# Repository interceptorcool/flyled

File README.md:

# flyled
Fly Led controller for WS281x

# Manual for config - temp_config/conf_prototype.txt

main module esp8266

Libraries:

JsonFiles:
https://bblanchon.github.io/ArduinoJson

NeoPixelBus:
https://github.com/Makuna/NeoPixelBus

# change
global config: "INPUTS"

# add
action class: "RAND"

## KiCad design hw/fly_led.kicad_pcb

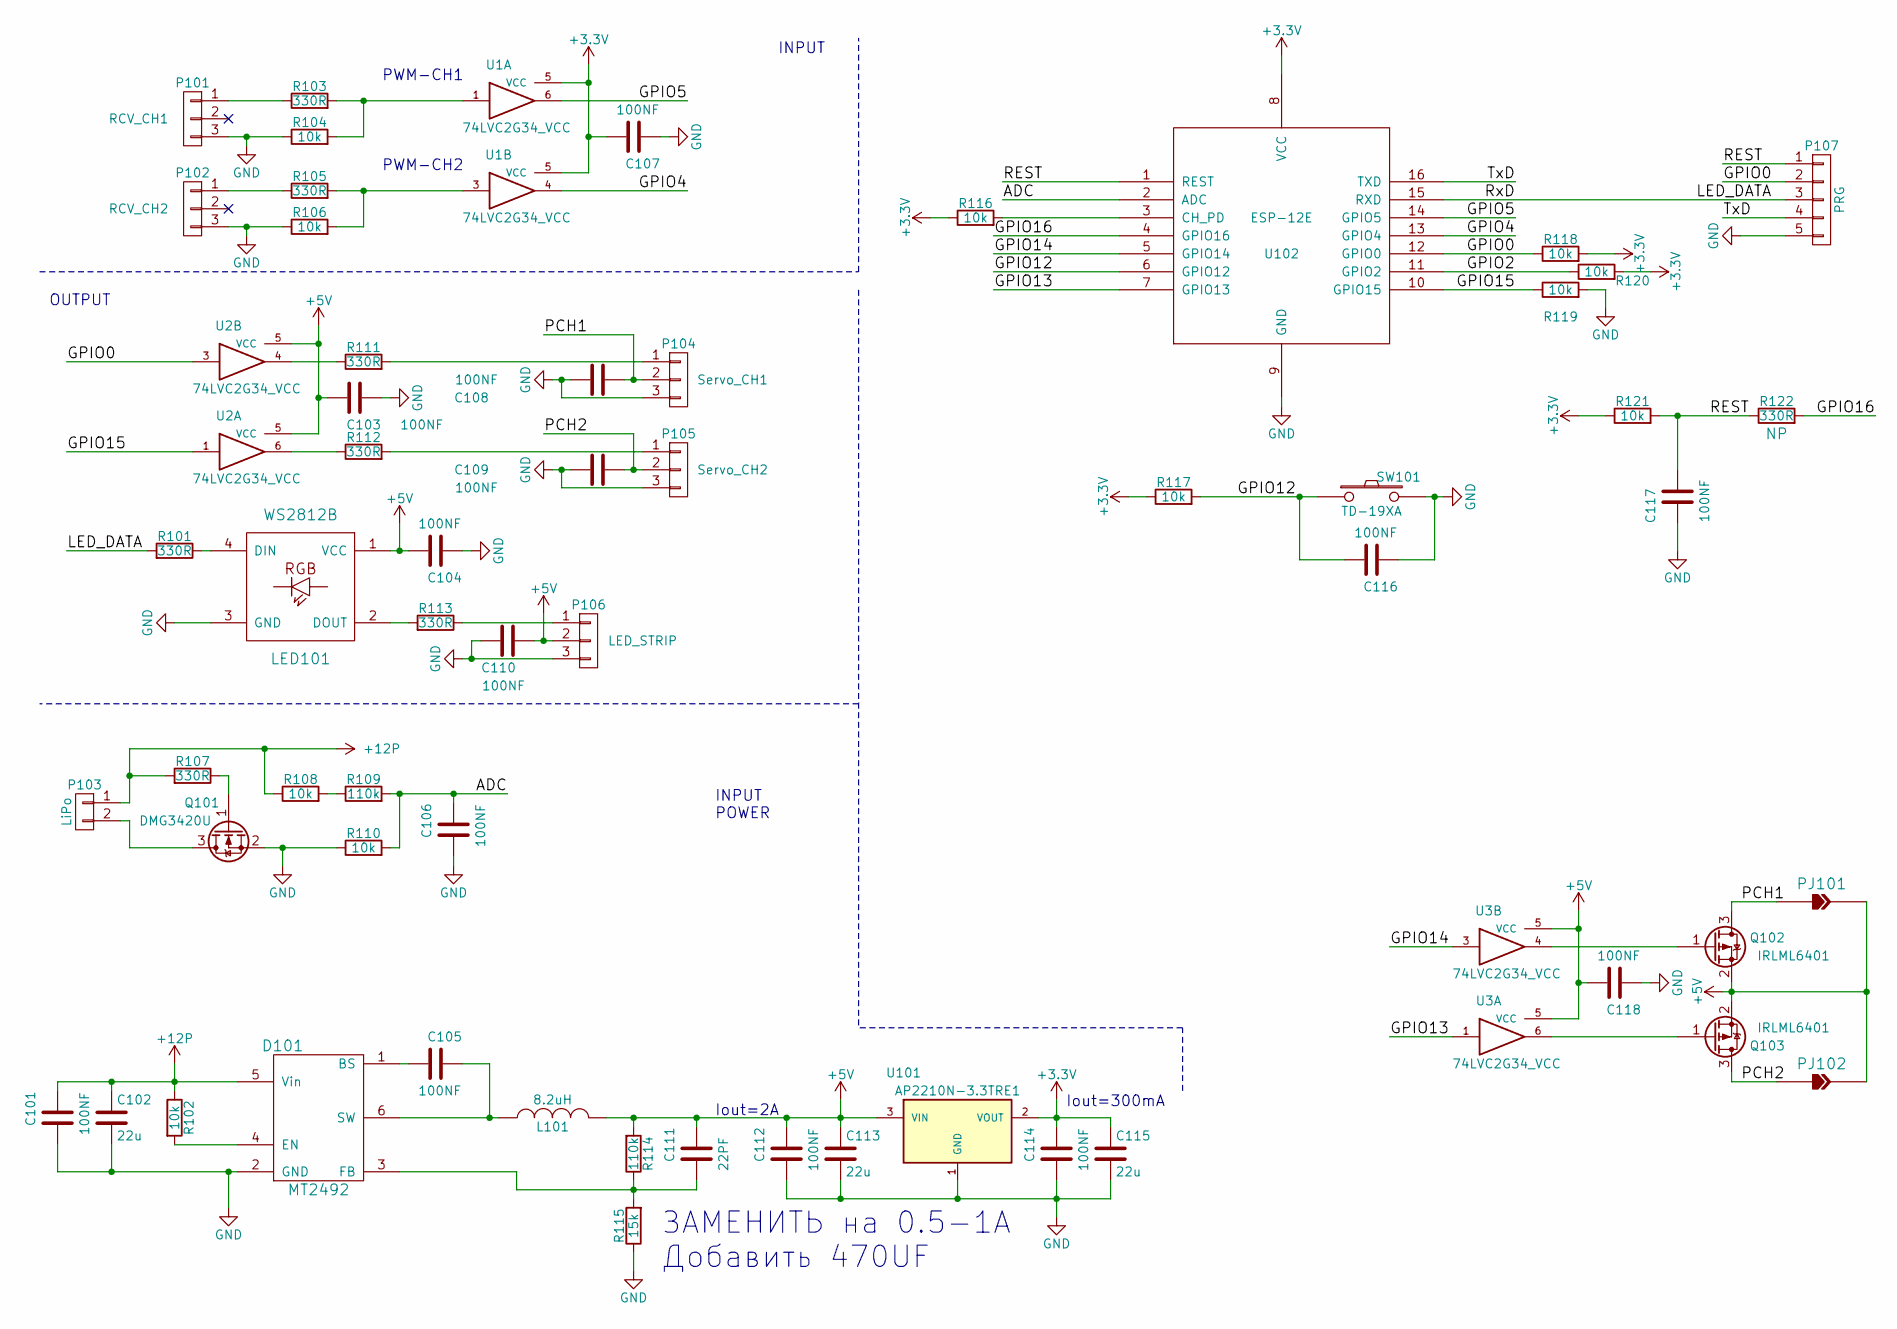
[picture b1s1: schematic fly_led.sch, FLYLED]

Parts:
C101, C103, C104, C105, C106, C107, C108, C109, C110, C112, C114, C116, C117, C118: 100NF; C_0603
C102, C113, C115: 22u; C_1210
C111: 22PF; C_0603
D101: MT2492; SOT-23-6
L101: 8.2uH; Choke_SMD_10.4x10.4_H4.8
LED101: WS2812B
P101: RCV_CH1; Pin_Header_Straight_1x03_Pitch2.54mm
P102: RCV_CH2; Pin_Header_Straight_1x03_Pitch2.54mm
P103: LiPo; Pin_Header_Straight_1x02_Pitch2.54mm
P104: Servo_CH1; Pin_Header_Straight_1x03_Pitch2.54mm
P105: Servo_CH2; Pin_Header_Straight_1x03_Pitch2.54mm
P106: LED_STRIP; Pin_Header_Straight_1x03_Pitch2.54mm
P107: PRG; Pin_Header_Straight_1x05_Pitch1.27mm
PJ101, PJ102: PJP; Jumper_SOL_HP
Q101: DMG3420U; SOT-23
Q102, Q103: IRLML6401; SOT-23
R101, R103, R105, R107, R111, R112, R113, R122: 330R; R_0603
R102, R104, R106, R108, R110, R116, R117, R118, R119, R120, R121: 10k; R_0603
R109, R114: 110k; R_0603
R115: 15k; R_0603
SW101: TD-19XA; SW_SPST_EVQPE1
U1, U2, U3: 74LVC2G34_VCC; SOT-363_SC-70-6
U101: AP2210N-3.3TRE1; SOT-23
U102: ESP-12E; ESP-12E-SMD

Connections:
+3V3: C107.2, C114.1, C115.1, R116.1, R117.1, R118.2, R120.2, R121.1, U1.5 (VCC), U101.2 (VOUT), U102.8 (VCC)
+5V: C103.2, C104.2, C110.2, C111.1, C112.1, C113.1, C118.2, L101.2, LED101.1 (VCC), P106.2, PJ101.2 (J2), PJ102.2 (J2), Q102.2 (S), Q103.2 (S), R114.2, U2.5 (VCC), U3.5 (VCC), U101.3 (VIN)
+12P: C101.1, C102.1, D101.5 (Vin), P103.1, R102.1, R107.2, R108.1
/ADC: C106.1, R109.2, R110.2, U102.2 (ADC)
/GPIO0: P107.2, R118.1, U2.3, U102.12 (GPIO0)
/GPIO2: R120.1, U102.11 (GPIO2)
/GPIO4: U1.4, U102.13 (GPIO4)
/GPIO5: U1.6, U102.14 (GPIO5)
/GPIO12: C116.2, R117.2, SW101.1, U102.6 (GPIO12)
/GPIO13: U3.1, U102.7 (GPIO13)
/GPIO14: U3.3, U102.5 (GPIO14)
/GPIO15: R119.1, U2.1, U102.10 (GPIO15)
/GPIO16: R122.2, U102.4 (GPIO16)
/LED_DATA: P107.3, R101.2, U102.15 (RXD)
/PCH1: C108.2, P104.2, PJ101.1 (J1), Q102.3 (D)
/PCH2: C109.2, P105.2, PJ102.1 (J1), Q103.3 (D)
/REST: C117.2, P107.1, R121.2, R122.1, U102.1 (REST)
/TxD: P107.4, U102.16 (TXD)
GND: C101.2, C102.2, C103.1, C104.1, C106.2, C107.1, C108.1, C109.1, C110.1, C112.2, C113.2, C114.2, C115.2, C116.1, C117.1, C118.1, D101.2 (GND), LED101.3 (GND), P101.3, P102.3, P104.3, P105.3, P106.3, P107.5, Q101.2 (S), R104.1, R106.1, R110.1, R115.1, R119.2, SW101.2, U1.2 (GND), U2.2 (GND), U3.2 (GND), U101.1 (GND), U102.9 (GND)
unnamed: C105.1, D101.6 (SW), L101.1
unnamed: C105.2, D101.1 (BS)
unnamed: C111.2, D101.3 (FB), R114.1, R115.2
unnamed: D101.4 (EN), R102.2
unnamed: LED101.2 (DOUT), R113.2
unnamed: LED101.4 (DIN), R101.1
unnamed: P101.1, R103.1
unnamed: P102.1, R105.1
unnamed: P103.2, Q101.3 (D)
unnamed: P104.1, R111.2
unnamed: P105.1, R112.2
unnamed: P106.1, R113.1
unnamed: Q101.1 (G), R107.1
unnamed: Q102.1 (G), U3.4
unnamed: Q103.1 (G), U3.6
unnamed: R103.2, R104.2, U1.1
unnamed: R105.2, R106.2, U1.3
unnamed: R108.2, R109.1
unnamed: R111.1, U2.4
unnamed: R112.1, U2.6
unnamed: R116.2, U102.3 (CH_PD)

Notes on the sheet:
PWM-CH1
PWM-CH2
INPUT
OUTPUT
INPUT POWER
Iout=2A
Iout=300mA
ЗАМЕНИТЬ на 0.5-1А Добавить 470UF

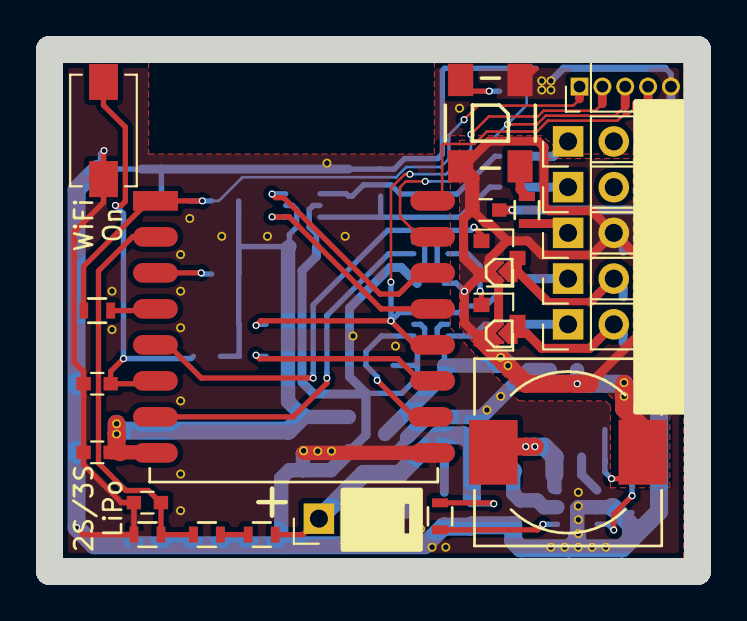
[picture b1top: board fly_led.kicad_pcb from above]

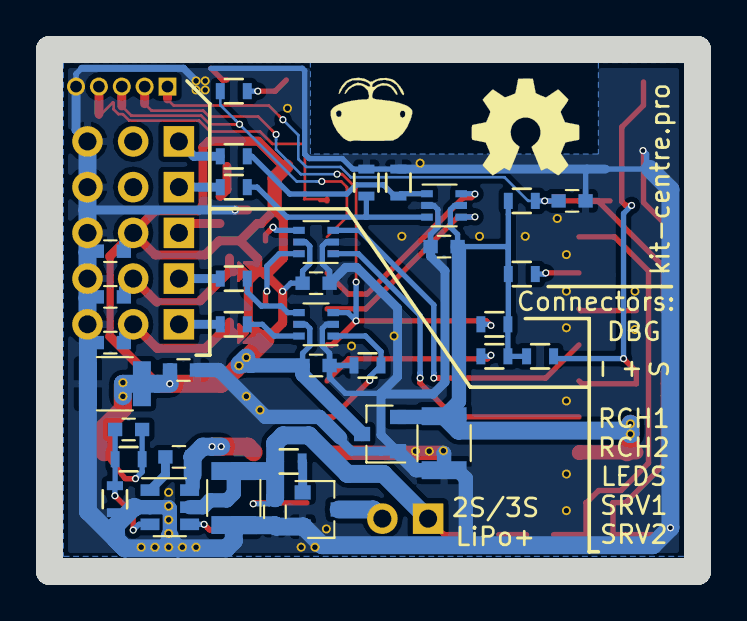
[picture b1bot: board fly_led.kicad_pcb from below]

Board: 2 copper layers, 36.0 x 29.0 mm, 61 parts (36 on the bottom side), 40 nets.
